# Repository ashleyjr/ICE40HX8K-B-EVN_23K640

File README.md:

# ICE40HX8K-B-EVN_23K640
23K640 SPI SRAM Expansion PCB for ICE40HX8K-B-EVN FPGA Dev Board

   - Also supports
 
      - 23K640 (64Kbit)
      - 23K256 (256Kbit)
      - 23LC1024 (1Mbit) -- ?

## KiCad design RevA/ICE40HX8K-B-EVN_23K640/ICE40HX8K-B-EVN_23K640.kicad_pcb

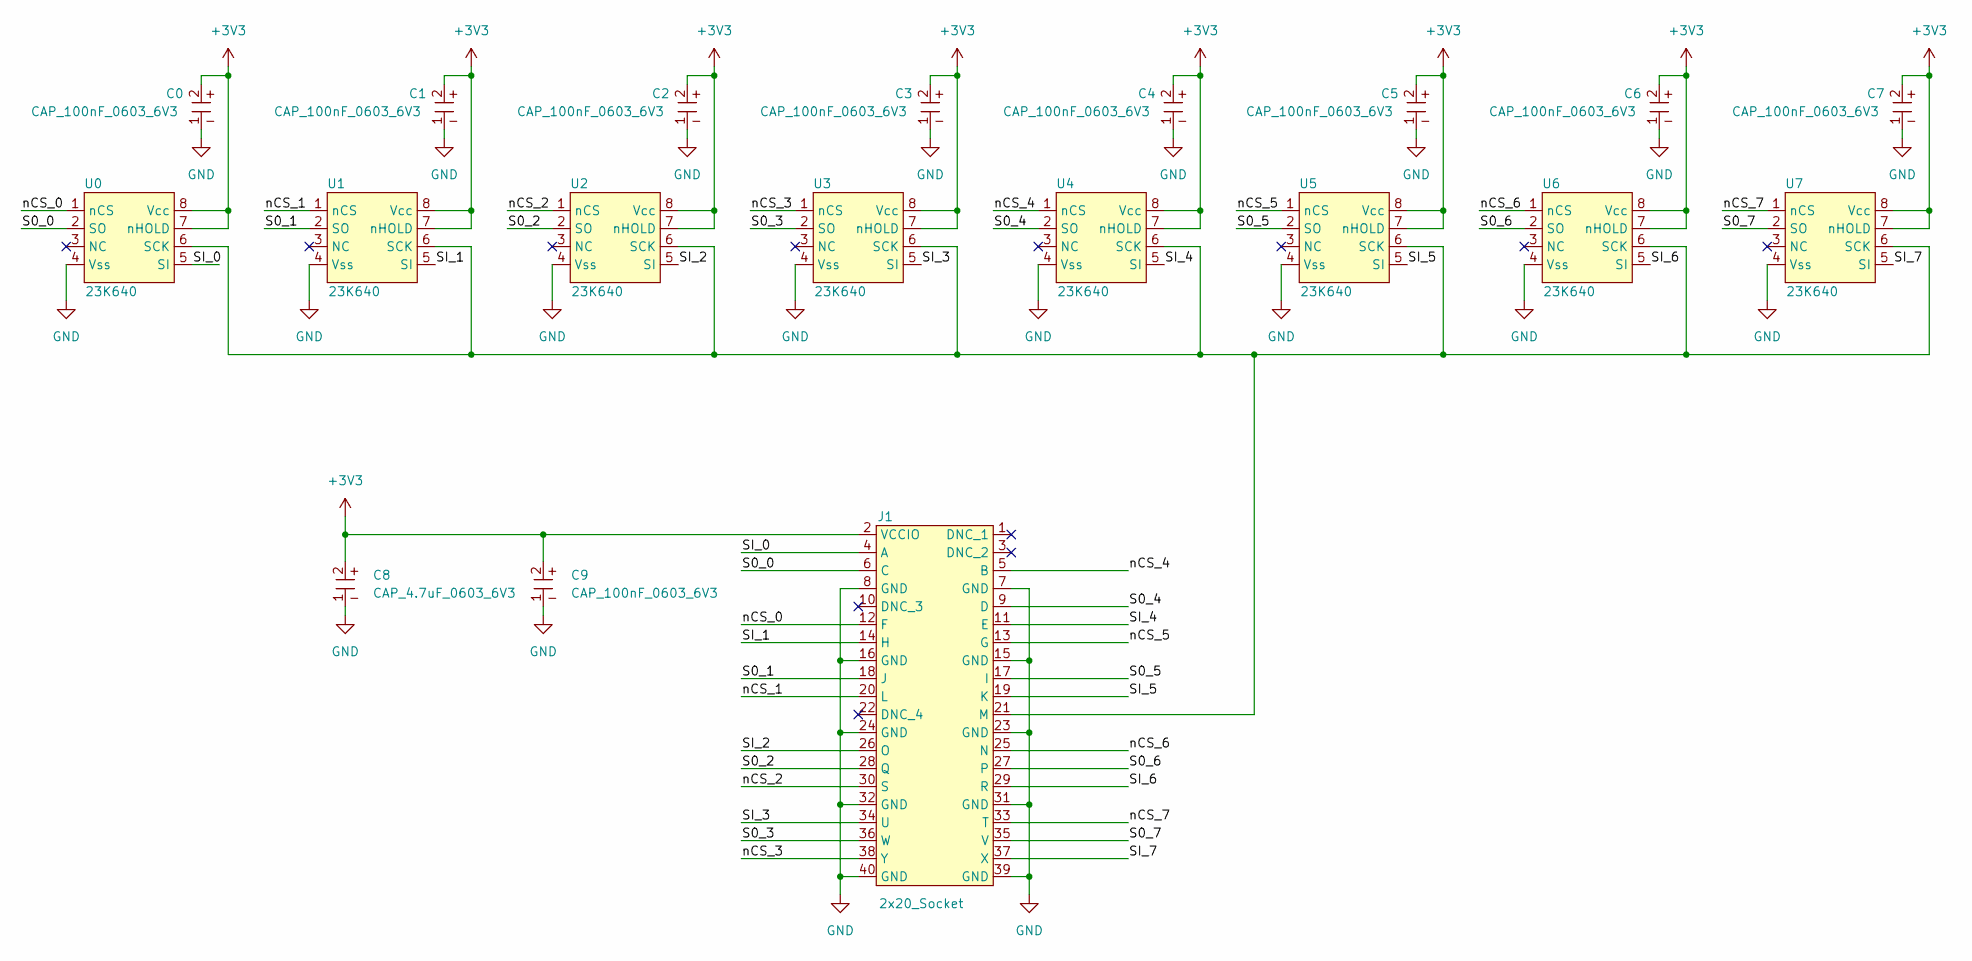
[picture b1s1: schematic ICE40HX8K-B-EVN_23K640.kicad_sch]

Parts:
C0, C1, C2, C3, C4, C5, C6, C7, C9: CAP_100nF_0603_6V3; 0603
C8: CAP_4.7uF_0603_6V3; 0603
J1: 2x20_Socket; 2x20_Header
U0, U1, U2, U3, U4, U5, U6, U7: 23K640

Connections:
+3V3: C0.2, C1.2, C2.2, C3.2, C4.2, C5.2, C6.2, C7.2, C8.2, C9.2, J1.2 (VCCIO), U0.7 (nHOLD), U0.8 (Vcc), U1.7 (nHOLD), U1.8 (Vcc), U2.7 (nHOLD), U2.8 (Vcc), U3.7 (nHOLD), U3.8 (Vcc), U4.7 (nHOLD), U4.8 (Vcc), U5.7 (nHOLD), U5.8 (Vcc), U6.7 (nHOLD), U6.8 (Vcc), U7.7 (nHOLD), U7.8 (Vcc)
/S0_0: J1.6 (C), U0.2 (SO)
/S0_1: J1.18 (J), U1.2 (SO)
/S0_2: J1.28 (Q), U2.2 (SO)
/S0_3: J1.36 (W), U3.2 (SO)
/S0_4: J1.9 (D), U4.2 (SO)
/S0_5: J1.17 (I), U5.2 (SO)
/S0_6: J1.27, U6.2 (SO)
/S0_7: J1.35 (V), U7.2 (SO)
/SI_0: J1.4 (A), U0.5 (SI)
/SI_1: J1.14 (H), U1.5 (SI)
/SI_2: J1.26 (O), U2.5 (SI)
/SI_3: J1.34 (U), U3.5 (SI)
/SI_4: J1.11 (E), U4.5 (SI)
/SI_5: J1.19 (K), U5.5 (SI)
/SI_6: J1.29 (R), U6.5 (SI)
/SI_7: J1.37 (X), U7.5 (SI)
/nCS_0: J1.12 (F), U0.1 (nCS)
/nCS_1: J1.20 (L), U1.1 (nCS)
/nCS_2: J1.30 (S), U2.1 (nCS)
/nCS_3: J1.38 (Y), U3.1 (nCS)
/nCS_4: J1.5 (B), U4.1 (nCS)
/nCS_5: J1.13 (G), U5.1 (nCS)
/nCS_6: J1.25 (N), U6.1 (nCS)
/nCS_7: J1.33 (T), U7.1 (nCS)
GND: C0.1, C1.1, C2.1, C3.1, C4.1, C5.1, C6.1, C7.1, C8.1, C9.1, J1.7 (GND), J1.8 (GND), J1.15 (GND), J1.16 (GND), J1.23 (GND), J1.24 (GND), J1.31 (GND), J1.32 (GND), J1.39 (GND), J1.40 (GND), U0.4 (Vss), U1.4 (Vss), U2.4 (Vss), U3.4 (Vss), U4.4 (Vss), U5.4 (Vss), U6.4 (Vss), U7.4 (Vss)
unnamed: J1.21 (M), U0.6 (SCK), U1.6 (SCK), U2.6 (SCK), U3.6 (SCK), U4.6 (SCK), U5.6 (SCK), U6.6 (SCK), U7.6 (SCK)

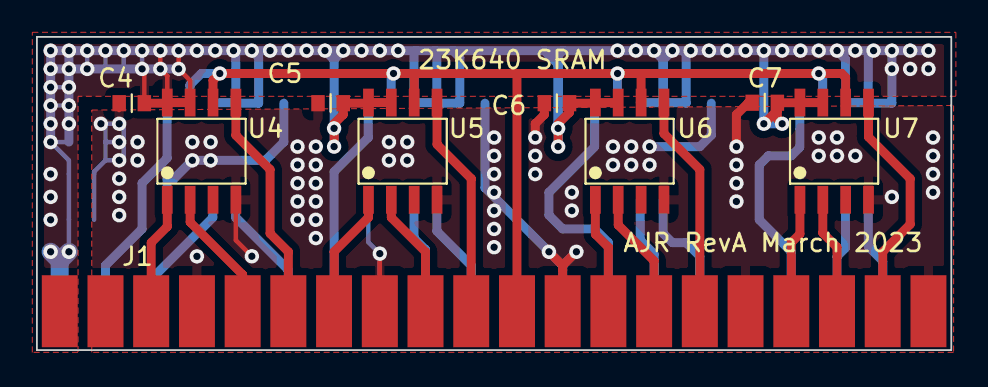
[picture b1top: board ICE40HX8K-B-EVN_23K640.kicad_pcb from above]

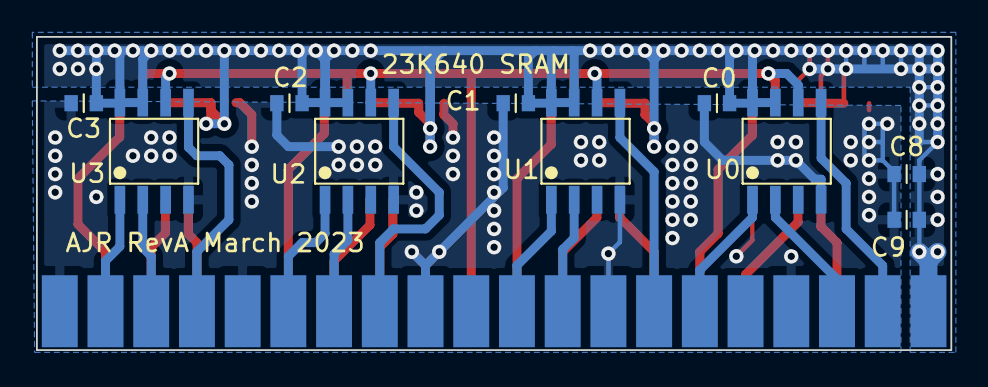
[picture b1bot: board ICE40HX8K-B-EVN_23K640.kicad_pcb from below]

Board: 2 copper layers, 50.8 x 17.4 mm, 19 parts (10 on the bottom side), 27 nets.

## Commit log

2023-03-18 test
2023-03-18 rev a
2023-03-18 mr backups
2023-03-18 ignore
2023-03-19 schematic done
2023-03-19 footprints
2023-03-20 routin
2023-03-20 rotate
2023-03-21 routed
2023-03-22 added fab output
2023-03-22 order
2023-05-01 started driver
2023-05-04 driver tests
2023-05-05 building
2023-05-06 build
2023-06-26 uart
2023-06-29 wr func
2023-07-03 first read/write test
2023-11-16 test update
2023-11-19 tests
